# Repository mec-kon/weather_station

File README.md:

# weather station
A simple weather station hardware for recording temperature, humidity, pressure and airquality.
The measured data can be provided over WiFi by using an ESP8266.
This hardware is available as open source hardware and released under GPL-3.0 license.

## Description
This is a circuitboard based on an ESP8266 for reading and evaluating sensor data.
By using an ESP8266, it is possible to evaluate sensor data directly and make it available via MQTT, for example.
This makes it very easy to integrate the weather station into existing smart home systems such as OpenHAB, Home Assistant or ioBroker.
Furthermore, the ESP8266 has an efficient low power mode, which allows battery operation or operation on a solar cell.

## Connections

The board has six connection terminals.
Three different for the power supply, two for the connection of external sensors and one for programming the ESP8266. 
The power can be supplied via micro-usb, usb-c or via a JST-XH plug.
If the JST-XH connector is used, the capacity of a battery connected to the board can also be measured.

## Applicable sensors

For temperature measurement, either an LM75 and a BME680 or BME280 can be used.
If the air quality is to be measured as well, a BME680 needs to be used, otherwise a cheaper BME280 sensor is sufficient for temperature, air pressure and humidity.

## Low Power

To wake up the ESP8266 from low power mode, the reset pin must be connected to GPIO16. On the board presented here this connection has already been made.

## Additional external sensors

On the backside of the board a male pin header as well as a 5-pin JST-XH connector are located, to which further I2C devices or similar can be connected.

## Programming

The ESP8266 can be programmed with an FTDI adapter. All needed pins can be found on the pin header on the front side.
Example Software is provided here:

## Measuring the battery level

To measure the battery level, it is recommended to use a TP4056 battery charger. An additional device for charging the battery can be connected to it.
The upper pin of the JST-XH connector then corresponds to B+, the middle to B- and the lower to GND (B- and OUT- on TP4056).

## Dimensions and Schematic

24.13mmx57.8mm

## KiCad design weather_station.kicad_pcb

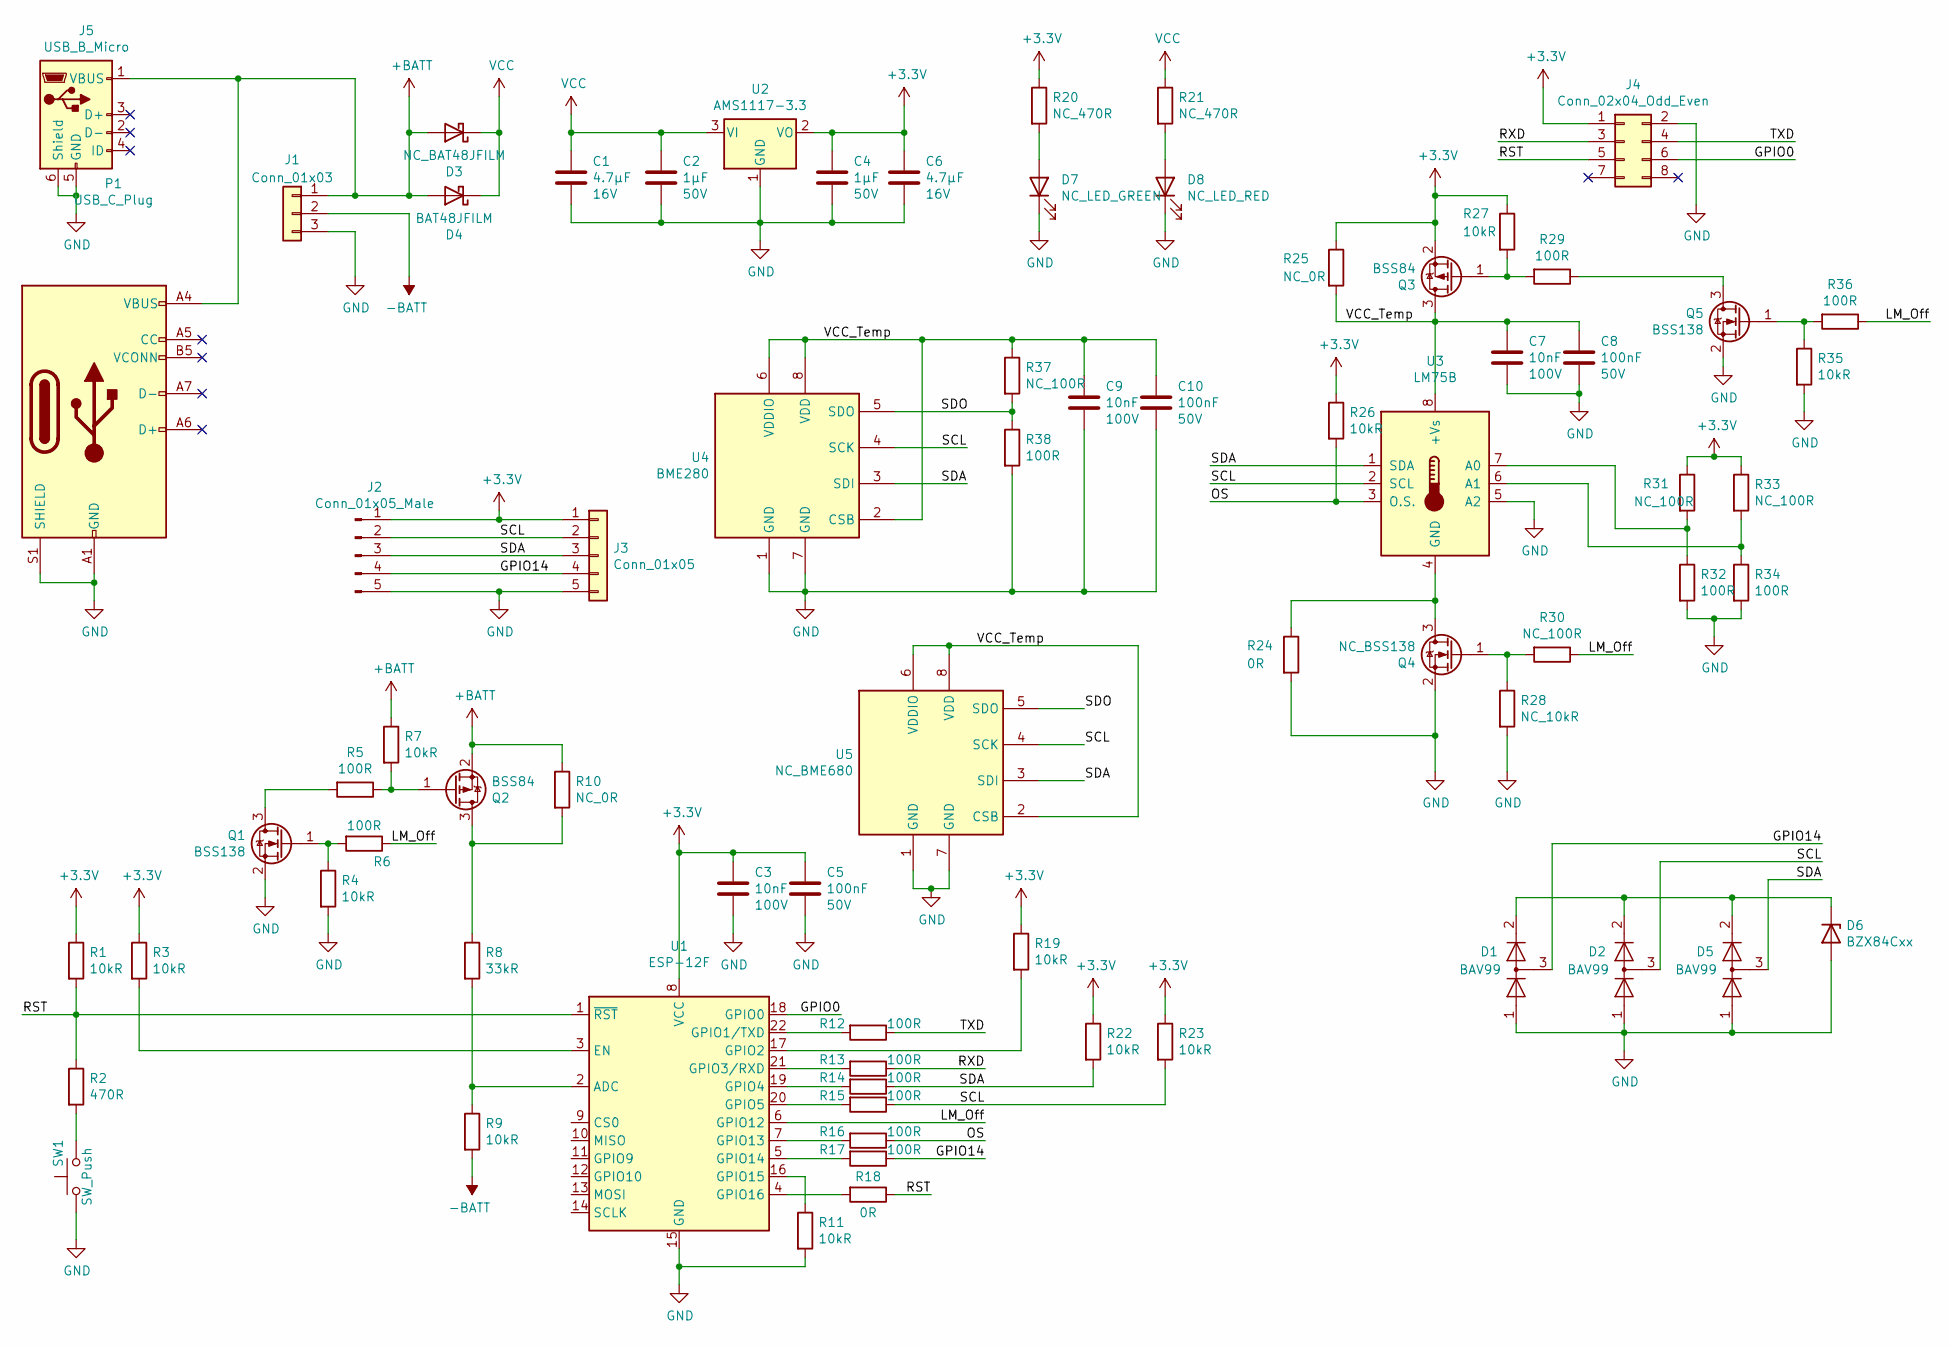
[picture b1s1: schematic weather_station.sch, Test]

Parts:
C1, C6: 4.7µF; C_1206_3216Metric
C2, C4: 1µF; C_0805_2012Metric
C3, C7, C9: 10nF; C_0805_2012Metric
C5, C8, C10: 100nF; C_0805_2012Metric
D1, D2, D5: BAV99; SOT-23
D3: NC_BAT48JFILM; D_SOD-323
D4: BAT48JFILM; D_SOD-323
D6: BZX84Cxx; D_SOT-23_ANK
D7: NC_LED_GREEN; LED_0805_2012Metric
D8: NC_LED_RED; LED_0805_2012Metric
J1: Conn_01x03; JST_XH_B3B-XH-A_1x03_P2.50mm_Vertical
J2: Conn_01x05_Male; PinHeader_1x05_P2.54mm_Vertical
J3: Conn_01x05; JST_XH_B5B-XH-A_1x05_P2.50mm_Vertical
J4: Conn_02x04_Odd_Even; PinHeader_2x04_P2.54mm_Vertical
J5: USB_B_Micro; USB_Micro-B_Molex_47346-0001
P1: USB_C_Plug; USB_C_Receptacle_XKB_U262-16XN-4BVC11
Q1, Q5: BSS138; SOT-23
Q2, Q3: BSS84; SOT-23
Q4: NC_BSS138; SOT-23
R1, R3, R4, R7, R9, R11, R19, R22, R23, R26, R27, R35: 10kR; R_0805_2012Metric
R2: 470R; R_0805_2012Metric
R5, R6, R12, R13, R14, R15, R16, R17, R29, R32, R34, R36, R38: 100R; R_0805_2012Metric
R8: 33kR; R_0805_2012Metric
R10, R25: NC_0R; R_0805_2012Metric
R18, R24: 0R; R_0805_2012Metric
R20, R21: NC_470R; R_0805_2012Metric
R28: NC_10kR; R_0805_2012Metric
R30, R31, R33, R37: NC_100R; R_0805_2012Metric
SW1: SW_Push; SW_Push_SPST_4x3x2
U1: ESP-12F; ESP-12E
U2: AMS1117-3.3; SOT-223-3_TabPin2
U3: LM75B; SSOP-8_3.9x5.05mm_P1.27mm
U4: BME280; Bosch_LGA-8_2.5x2.5mm_P0.65mm_ClockwisePinNumbering
U5: NC_BME680; Bosch_LGA-8_3x3mm_P0.8mm_ClockwisePinNumbering

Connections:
+3V3: C3.1, C4.1, C5.1, C6.1, J2.1, J3.1, J4.1, Q3.2 (S), R1.1, R3.1, R19.1, R20.1, R22.1, R23.1, R25.1, R26.1, R27.1, R31.1, R33.1, U1.8 (VCC), U2.2 (VO)
+BATT: D3.2 (A), D4.2 (A), J1.1, J5.1 (VBUS), P1.A4 (VBUS), P1.A9 (VBUS), P1.B4 (VBUS), P1.B9 (VBUS), Q2.2 (S), R7.1, R10.1
-BATT: J1.2, R9.2
/GPIO0: J4.6, U1.18 (GPIO0)
/GPIO14: D1.3 (K), J2.4, J3.4, R17.1
/LM_Off: R6.1, R30.1, R36.1, U1.6 (GPIO12)
/OS: R16.1, R26.2, U3.3 (O.S.)
/RST: J4.5, R1.2, R2.1, R18.1, U1.1 (~RST)
/RXD: J4.3, R13.1
/SCL: D2.3 (K), J2.2, J3.2, R15.1, R23.2, U3.2 (SCL), U4.4 (SCK), U5.4 (SCK)
/SDA: D5.3 (K), J2.3, J3.3, R14.1, R22.2, U3.1 (SDA), U4.3 (SDI), U5.3 (SDI)
/SDO: R37.2, R38.1, U4.5 (SDO), U5.5 (SDO)
/TXD: J4.4, R12.1
/VCC_Temp: C7.1, C8.1, C9.1, C10.1, Q3.3 (D), R25.2, R37.1, U3.8 (+Vs), U4.2 (CSB), U4.6 (VDDIO), U4.8 (VDD), U5.2 (CSB), U5.6 (VDDIO), U5.8 (VDD)
GND: C1.2, C2.2, C3.2, C4.2, C5.2, C6.2, C7.2, C8.2, C9.2, C10.2, D1.1 (K), D2.1 (K), D5.1 (K), D6.2 (A), D7.1 (K), D8.1 (K), J1.3, J2.5, J3.5, J4.2, J5.5 (GND), J5.6 (Shield), P1.A1 (GND), P1.A12 (GND), P1.B1 (GND), P1.B12 (GND), P1.S1 (SHIELD), Q1.2 (S), Q4.2 (S), Q5.2 (S), R4.2, R11.2, R24.2, R28.2, R32.2, R34.2, R35.2, R38.2, SW1.1, U1.15 (GND), U2.1 (GND), U3.5 (A2), U4.1 (GND), U4.7 (GND), U5.1 (GND), U5.7 (GND)
unnamed: D1.2 (A), D2.2 (A), D5.2 (A), D6.1 (K)
unnamed: D7.2 (A), R20.2
unnamed: D8.2 (A), R21.2
unnamed: Q1.1 (G), R4.1, R6.2
unnamed: Q1.3 (D), R5.2
unnamed: Q2.1 (G), R5.1, R7.2
unnamed: Q2.3 (D), R8.1, R10.2
unnamed: Q3.1 (G), R27.2, R29.2
unnamed: Q4.1 (G), R28.1, R30.2
unnamed: Q4.3 (D), R24.1, U3.4 (GND)
unnamed: Q5.1 (G), R35.1, R36.2
unnamed: Q5.3 (D), R29.1
unnamed: R2.2, SW1.2
unnamed: R3.2, U1.3 (EN)
unnamed: R8.2, R9.1, U1.2 (ADC)
unnamed: R11.1, U1.16 (GPIO15)
unnamed: R12.2, U1.22 (GPIO1/TXD)
unnamed: R13.2, U1.21 (GPIO3/RXD)
unnamed: R14.2, U1.19 (GPIO4)
unnamed: R15.2, U1.20 (GPIO5)
unnamed: R16.2, U1.7 (GPIO13)
unnamed: R17.2, U1.5 (GPIO14)
unnamed: R18.2, U1.4 (GPIO16)
unnamed: R19.2, U1.17 (GPIO2)
unnamed: R31.2, R32.1, U3.7 (A0)
unnamed: R33.2, R34.1, U3.6 (A1)
VCC: C1.1, C2.1, D3.1 (K), D4.1 (K), R21.1, U2.3 (VI)

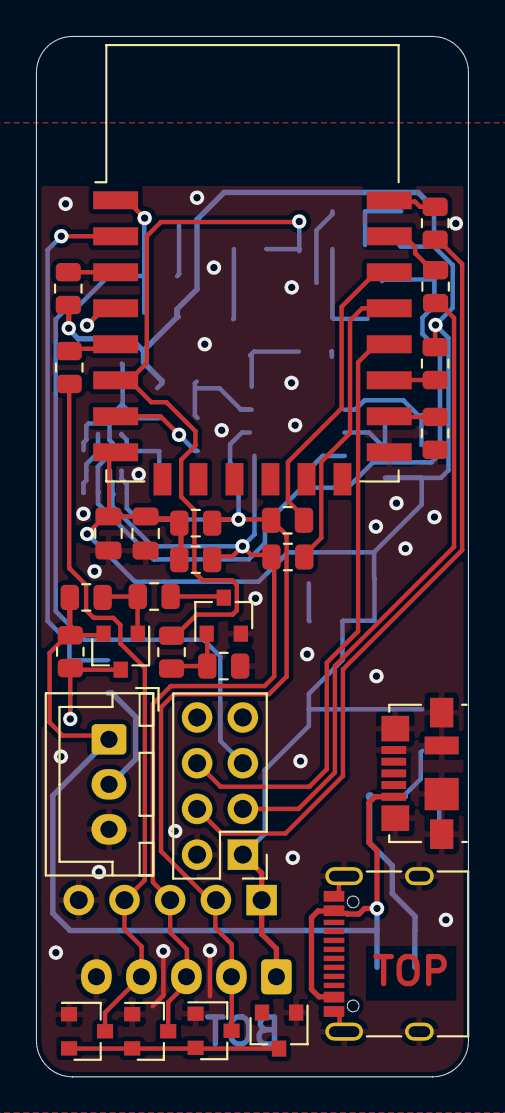
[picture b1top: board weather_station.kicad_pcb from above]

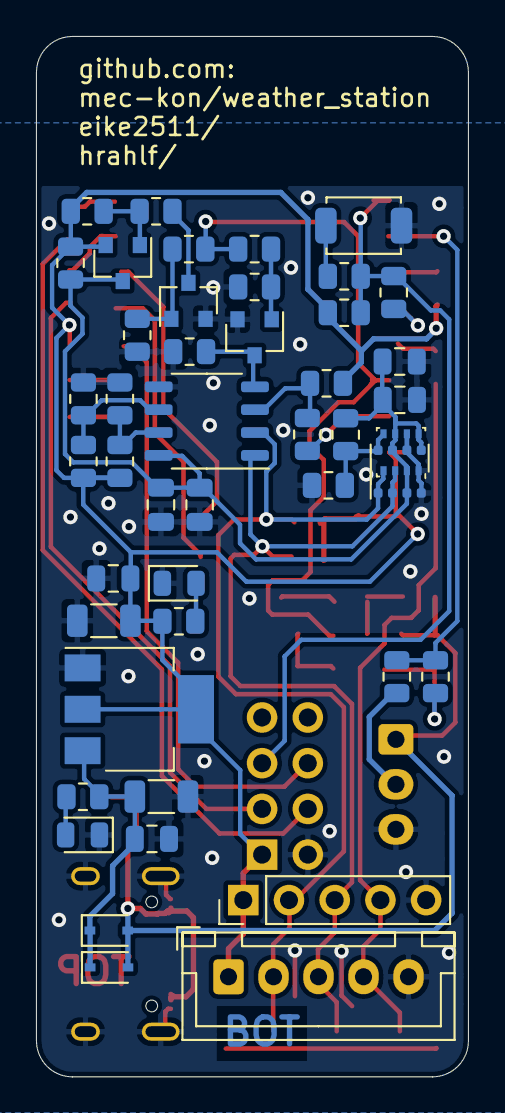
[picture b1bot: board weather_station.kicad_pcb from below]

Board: 2 copper layers, 24.0 x 57.8 mm, 73 parts (45 on the bottom side), 42 nets.

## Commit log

2020-12-10 edit silkscreen
2020-12-10 added gerber and drill files
2020-12-15 Add active html bom
2020-12-16 updated demo image file
2020-12-19 changed 3d model path
2020-12-21 Edit NC Components and update footprints
